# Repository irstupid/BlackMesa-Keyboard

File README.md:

# Keyboard Project

the first week of hack clubs half life thing.

i have a friend who asked me to make a keyboard for him and i was like "oh sure that sounds fun" and now i am finaly getting around to it

- it runs on a raspberry pi pico using QMK as its main firmware (more details in the firmware section once i do that)
- it is TKL
- it has 90 neopixle addressable LEDS
- it has a custom case (also unfinished, will update once done)

## THE PICO USB
after writing this section i realized i got maybe a little annoyed and crashed out a little, but im keeping it like this because i think its valid to get a little annoyed that my project has been rejected like four times for something i fixed three times ago, but dont take it personally, i completely understand you are probably trying to get through as many projects in as little time as possible and some things slip through the cracks

ok yall are really REALLY giving me hell about my pico usb placement and i have justified and explained how it will work like FOUR TIMES but im STILL REJECTED FOR IT so here we go again, if you reject me for this once again i swear to god i am going to just straight up leave this whole thing.

the board is suspended in the case:

the pico is attached to the bottom of the board. it is not colliding with the bottom of the case because the board is suspended. the usb can plug into the pico because the pico board has a thickness (1mm to be exact, specified by the datasheet here https://pip-assets.raspberrypi.com/categories/610-raspberry-pi-pico/documents/RP-008307-DS-3-pico-datasheet.pdf on page 7) and i have a usb plug that has a exterior thickness of less than 1mm, allowing it to fit between the pico and board:

the cable will exit the case through the back. this is a top view of the cable exiting the board. the cable runs bellow the PCB. I reiterate, THE PCB IS SUSPENDED. THERE IS SPACE BENEATH IT. THE CABLE GOES IN THAT SPACE:

this is a full side profile of the case. As you can see, the PCB is suspended by the key plate, the pico is soldered to the underside of the PCB, the cable plugs into the usb on the pcio, and the cable runs beneath the PCB and out of the case:

THIS. WILL. WORK. I am 100% sure this will work. i have sextuple checked all of my work. everything fits. IT. WILL. WORK. if you are incapable of understanding that i recommend going to the local kindergarten and retaking shapes and colors instead of failing me based on your incompetence. 

Also, you marked off my BOM for not including a SINGLE 6.3mm THT resisitor. You can find this resistor in literally any electronics kit ever. breadboards come with them, arduinos come with them, even fucking leds come with them. they are everywhere. my school has a literal cabinet full of them. i have a few thousand of them. i would be willing to bet that you have at least a few hundred of them to. you could probably find them laying on the street, i probably have 3 on my floor somewhere, i wouldn't be surprised if i have one inside of my body. you can find this SINGLE component basically anywhere. you can barely even buy them individually. they cost like literally less than a cent. here is a pack of 2600 of them for like $15 https://www.amazon.com/dp/B085NQZNTY?lv=shuf&channelId=500&plpRedirect=mhFallback. I am (obviously) supplying this myself. whats next? do i have to include the solder i intend to use for this project in my BOM? the electricity i use for the soldering iron? the wires i use to patch things together? the usb cable i use to program the pcio? because all of those things have a significantly bigger impact on the total cost of this project. it is a SINGLE FUCKING RESISTOR. ITS NOT EVEN A NECESSARY COMPONENT, it just helps debounce the address line (which is only like 30mm long so it barely matters). the resistance dosent mater. it could be anywhere between a 220 and a 10k resistor. i could probably construct this component myself with a paperclip. like im sorry for the crash out but seriously is this the hill you are going to kill me on? 

## Schematic

also here is the row/column layout if you were wondering

## PCB

i was initially going to add a silkscreen but ran out of inspiration and time. i might still do that it have have any ideas.
the BOM only has the board and none of the parts because i am sourcing those externally.
the usbc on the pico pointing inward is intentional, the cable will go along the bottom and through the back side of the case.

also sorry about not fixing the issues with the PCB i fixed them but then forgot to commit, everything should be updated now.

## Firmware
it will use QMK for the keyboard and some custom program for controlling the LEDS on a separate core.
i will work on the firmware once i have a pico and board to test on

## Case
the case will be made from a 3d printed part and a sanded acrylic key plate. here is a rough sketch

everything will be machined in house at my school. i will add more details once done

.

.

.

.

i was initially skeptical of markdowns but i actually really like how they handle formatting, i might start using them more. hopefully this readme is ok!

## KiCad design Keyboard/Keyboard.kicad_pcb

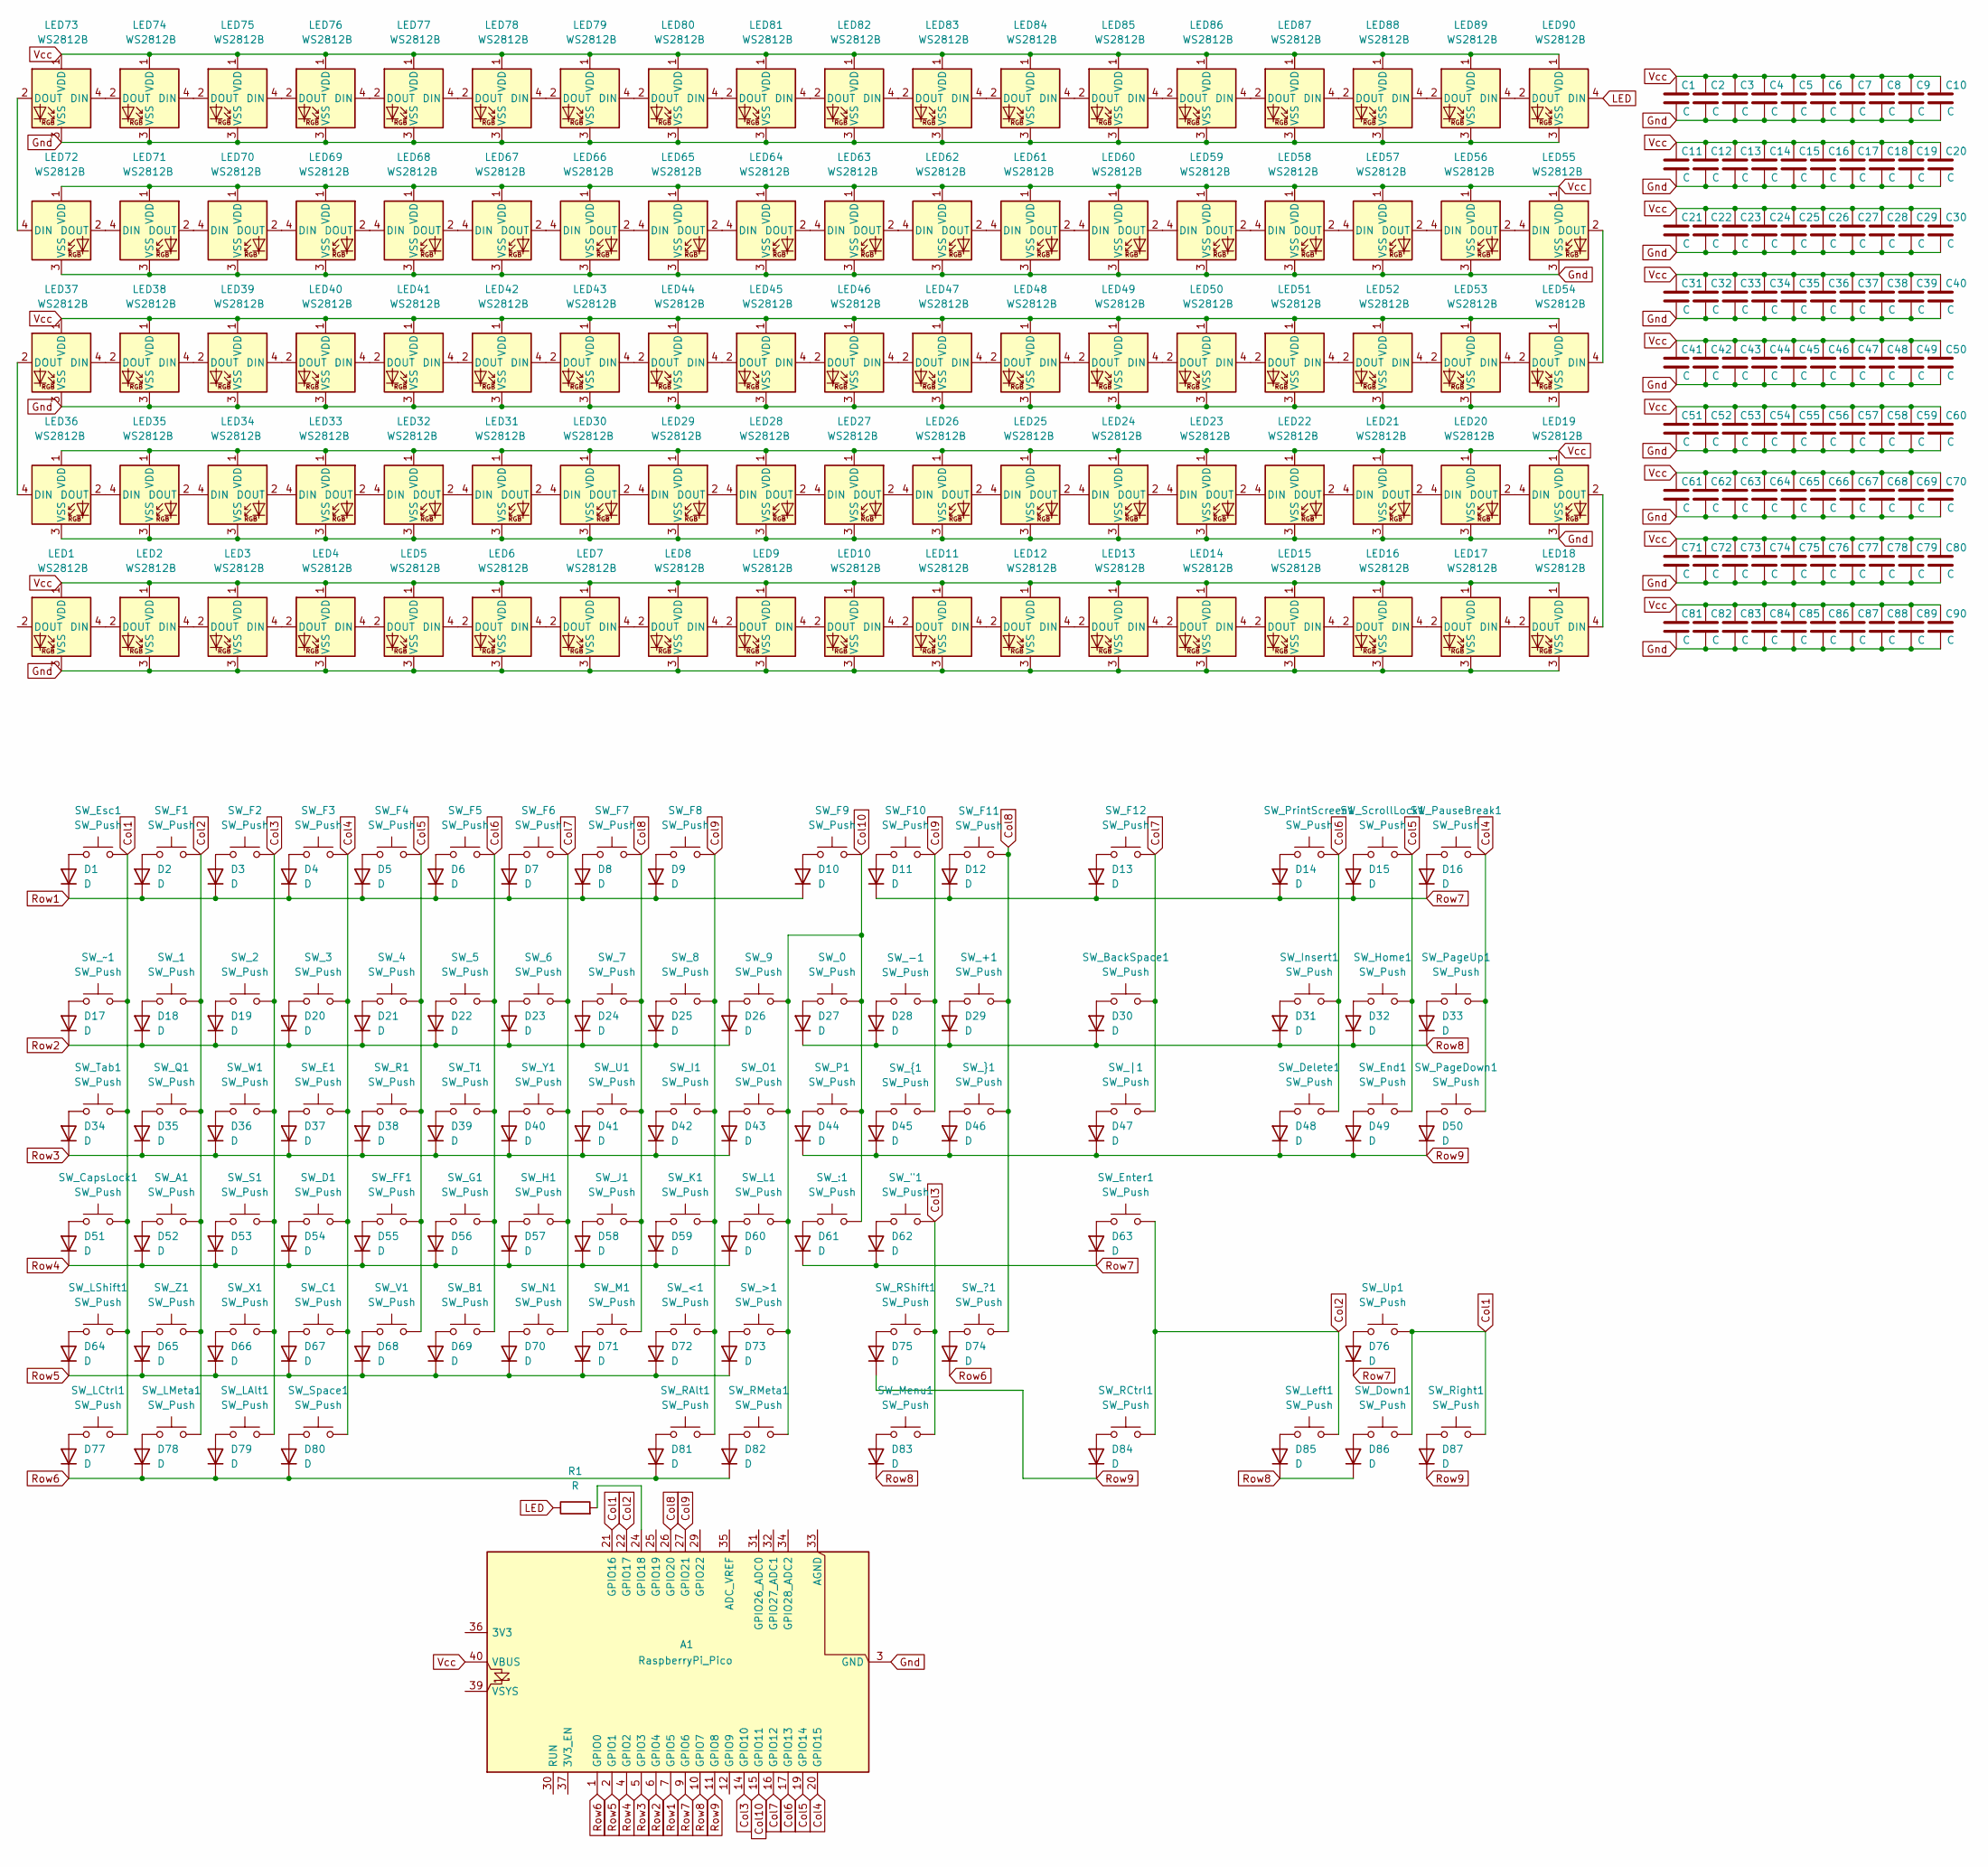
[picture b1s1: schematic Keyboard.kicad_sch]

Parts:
A1: RaspberryPi_Pico; RaspberryPi_Pico_Common_SMD
C1, C2, C3, C4, C5, C6, C7, C8, C9, C10, C11, C12, C13, C14, C15, C16, C17, C18, C19, C20, C21, C22, C23, C24, C25, C26, C27, C28, C29, C30, C31, C32, C33, C34, C35, C36, C37, C38, C39, C40, C41, C42, C43, C44, C45, C46, C47, C48, C49, C50, C51, C52, C53, C54, C55, C56, C57, C58, C59, C60, C61, C62, C63, C64, C65, C66, C67, C68, C69, C70, C71, C72, C73, C74, C75, C76, C77, C78, C79, C80, C81, C82, C83, C84, C85, C86, C87, C88, C89, C90: C; C_0201_0603Metric_Pad0.64x0.40mm_HandSolder
D1, D2, D3, D4, D5, D6, D7, D8, D9, D10, D11, D12, D13, D14, D15, D16, D17, D18, D19, D20, D21, D22, D23, D24, D25, D26, D27, D28, D29, D30, D31, D32, D33, D34, D35, D36, D37, D38, D39, D40, D41, D42, D43, D44, D45, D46, D47, D48, D49, D50, D51, D52, D53, D54, D55, D56, D57, D58, D59, D60, D61, D62, D63, D64, D65, D66, D67, D68, D69, D70, D71, D72, D73, D74, D75, D76, D77, D78, D79, D80, D81, D82, D83, D84, D85, D86, D87: D; D_SMA
LED1, LED2, LED3, LED4, LED5, LED6, LED7, LED8, LED9, LED10, LED11, LED12, LED13, LED14, LED15, LED16, LED17, LED18, LED19, LED20, LED21, LED22, LED23, LED24, LED25, LED26, LED27, LED28, LED29, LED30, LED31, LED32, LED33, LED34, LED35, LED36, LED37, LED38, LED39, LED40, LED41, LED42, LED43, LED44, LED45, LED46, LED47, LED48, LED49, LED50, LED51, LED52, LED53, LED54, LED55, LED56, LED57, LED58, LED59, LED60, LED61, LED62, LED63, LED64, LED65, LED66, LED67, LED68, LED69, LED70, LED71, LED72, LED73, LED74, LED75, LED76, LED77, LED78, LED79, LED80, LED81, LED82, LED83, LED84, LED85, LED86, LED87, LED88, LED89, LED90: WS2812B; LED_WS2812B_PLCC4_5.0x5.0mm_P3.2mm
R1: R; R_Axial_DIN0207_L6.3mm_D2.5mm_P7.62mm_Horizontal
SW_0, SW_1, SW_2, SW_3, SW_4, SW_5, SW_6, SW_7, SW_8, SW_9: SW_Push; SW_Cherry_MX_1.00u_PCB
SW_"1: SW_Push; SW_Cherry_MX_1.00u_PCB
SW_+1: SW_Push; SW_Cherry_MX_1.00u_PCB
SW_-1: SW_Push; SW_Cherry_MX_1.00u_PCB
SW_:1: SW_Push; SW_Cherry_MX_1.00u_PCB
SW_<1: SW_Push; SW_Cherry_MX_1.00u_PCB
SW_>1: SW_Push; SW_Cherry_MX_1.00u_PCB
SW_?1: SW_Push; SW_Cherry_MX_1.00u_PCB
SW_A1: SW_Push; SW_Cherry_MX_1.00u_PCB
SW_B1: SW_Push; SW_Cherry_MX_1.00u_PCB
SW_BackSpace1: SW_Push; SW_Cherry_MX_2.00u_PCB
SW_C1: SW_Push; SW_Cherry_MX_1.00u_PCB
SW_CapsLock1: SW_Push; SW_Cherry_MX_1.75u_PCB
SW_D1: SW_Push; SW_Cherry_MX_1.00u_PCB
SW_Delete1: SW_Push; SW_Cherry_MX_1.00u_PCB
SW_Down1: SW_Push; SW_Cherry_MX_1.00u_PCB
SW_E1: SW_Push; SW_Cherry_MX_1.00u_PCB
SW_End1: SW_Push; SW_Cherry_MX_1.00u_PCB
SW_Enter1: SW_Push; SW_Cherry_MX_2.25u_PCB
SW_Esc1: SW_Push; SW_Cherry_MX_1.00u_PCB
SW_F1, SW_F2, SW_F3, SW_F4, SW_F5, SW_F6, SW_F7, SW_F8, SW_F9, SW_F10, SW_F11, SW_F12: SW_Push; SW_Cherry_MX_1.00u_PCB
SW_FF1: SW_Push; SW_Cherry_MX_1.00u_PCB
SW_G1: SW_Push; SW_Cherry_MX_1.00u_PCB
SW_H1: SW_Push; SW_Cherry_MX_1.00u_PCB
SW_Home1: SW_Push; SW_Cherry_MX_1.00u_PCB
SW_I1: SW_Push; SW_Cherry_MX_1.00u_PCB
SW_Insert1: SW_Push; SW_Cherry_MX_1.00u_PCB
SW_J1: SW_Push; SW_Cherry_MX_1.00u_PCB
SW_K1: SW_Push; SW_Cherry_MX_1.00u_PCB
SW_L1: SW_Push; SW_Cherry_MX_1.00u_PCB
SW_LAlt1: SW_Push; SW_Cherry_MX_1.25u_PCB
SW_LCtrl1: SW_Push; SW_Cherry_MX_1.25u_PCB
SW_LMeta1: SW_Push; SW_Cherry_MX_1.25u_PCB
SW_LShift1: SW_Push; SW_Cherry_MX_2.25u_PCB
SW_Left1: SW_Push; SW_Cherry_MX_1.00u_PCB
SW_M1: SW_Push; SW_Cherry_MX_1.00u_PCB
SW_Menu1: SW_Push; SW_Cherry_MX_1.25u_Plate
SW_N1: SW_Push; SW_Cherry_MX_1.00u_PCB
SW_O1: SW_Push; SW_Cherry_MX_1.00u_PCB
SW_P1: SW_Push; SW_Cherry_MX_1.00u_PCB
SW_PageDown1: SW_Push; SW_Cherry_MX_1.00u_PCB
SW_PageUp1: SW_Push; SW_Cherry_MX_1.00u_PCB
SW_PauseBreak1: SW_Push; SW_Cherry_MX_1.00u_PCB
SW_PrintScreen1: SW_Push; SW_Cherry_MX_1.00u_PCB
SW_Q1: SW_Push; SW_Cherry_MX_1.00u_PCB
SW_R1: SW_Push; SW_Cherry_MX_1.00u_PCB
SW_RAlt1: SW_Push; SW_Cherry_MX_1.25u_PCB
SW_RCtrl1: SW_Push; SW_Cherry_MX_1.25u_PCB
SW_RMeta1: SW_Push; SW_Cherry_MX_1.25u_PCB
SW_RShift1: SW_Push; SW_Cherry_MX_2.75u_PCB
SW_Right1: SW_Push; SW_Cherry_MX_1.00u_PCB
SW_S1: SW_Push; SW_Cherry_MX_1.00u_PCB
SW_ScrollLock1: SW_Push; SW_Cherry_MX_1.00u_PCB
SW_Space1: SW_Push; SW_Cherry_MX_6.25u_PCB
SW_T1: SW_Push; SW_Cherry_MX_1.00u_PCB
SW_Tab1: SW_Push; SW_Cherry_MX_1.50u_PCB
SW_U1: SW_Push; SW_Cherry_MX_1.00u_PCB
SW_Up1: SW_Push; SW_Cherry_MX_1.00u_PCB
SW_V1: SW_Push; SW_Cherry_MX_1.00u_PCB
SW_W1: SW_Push; SW_Cherry_MX_1.00u_PCB
SW_X1: SW_Push; SW_Cherry_MX_1.00u_PCB
SW_Y1: SW_Push; SW_Cherry_MX_1.00u_PCB
SW_Z1: SW_Push; SW_Cherry_MX_1.00u_PCB
SW_{1: SW_Push; SW_Cherry_MX_1.00u_PCB
SW_|1: SW_Push; SW_Cherry_MX_1.50u_PCB
SW_}1: SW_Push; SW_Cherry_MX_1.00u_PCB
SW_~1: SW_Push; SW_Cherry_MX_1.00u_PCB

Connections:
Col1: A1.21 (GPIO16), SW_CapsLock1.1, SW_Down1.1, SW_Esc1.1, SW_LCtrl1.1, SW_LShift1.1, SW_Right1.1, SW_Tab1.1, SW_Up1.1, SW_~1.1
Col2: A1.22 (GPIO17), SW_1.1, SW_A1.1, SW_Enter1.1, SW_F1.1, SW_LMeta1.1, SW_Left1.1, SW_Q1.1, SW_RCtrl1.1, SW_Z1.1
Col3: A1.14 (GPIO10), SW_2.1, SW_"1.1, SW_F2.1, SW_LAlt1.1, SW_Menu1.1, SW_RShift1.1, SW_S1.1, SW_W1.1, SW_X1.1
Col4: A1.20 (GPIO15), SW_3.1, SW_C1.1, SW_D1.1, SW_E1.1, SW_F3.1, SW_PageDown1.1, SW_PageUp1.1, SW_PauseBreak1.1, SW_Space1.1
Col5: A1.19 (GPIO14), SW_4.1, SW_End1.1, SW_F4.1, SW_FF1.1, SW_Home1.1, SW_R1.1, SW_ScrollLock1.1, SW_V1.1
Col6: A1.17 (GPIO13), SW_5.1, SW_B1.1, SW_Delete1.1, SW_F5.1, SW_G1.1, SW_Insert1.1, SW_PrintScreen1.1, SW_T1.1
Col7: A1.16 (GPIO12), SW_6.1, SW_BackSpace1.1, SW_F6.1, SW_F12.1, SW_H1.1, SW_N1.1, SW_Y1.1, SW_|1.1
Col8: A1.26 (GPIO20), SW_7.1, SW_+1.1, SW_?1.1, SW_F7.1, SW_F11.1, SW_J1.1, SW_M1.1, SW_U1.1, SW_}1.1
Col9: A1.27 (GPIO21), SW_8.1, SW_-1.1, SW_<1.1, SW_F8.1, SW_F10.1, SW_I1.1, SW_K1.1, SW_RAlt1.1, SW_{1.1
Col10: A1.15 (GPIO11), SW_0.1, SW_9.1, SW_:1.1, SW_>1.1, SW_F9.1, SW_L1.1, SW_O1.1, SW_P1.1, SW_RMeta1.1
Gnd: A1.3 (GND), A1.8 (GND), A1.13 (GND), A1.18 (GND), A1.23 (GND), A1.28 (GND), A1.38 (GND), C1.2, C2.2, C3.2, C4.2, C5.2, C6.2, C7.2, C8.2, C9.2, C10.2, C11.2, C12.2, C13.2, C14.2, C15.2, C16.2, C17.2, C18.2, C19.2, C20.2, C21.2, C22.2, C23.2, C24.2, C25.2, C26.2, C27.2, C28.2, C29.2, C30.2, C31.2, C32.2, C33.2, C34.2, C35.2, C36.2, C37.2, C38.2, C39.2, C40.2, C41.2, C42.2, C43.2, C44.2, C45.2, C46.2, C47.2, C48.2, C49.2, C50.2, C51.2, C52.2, C53.2, C54.2, C55.2, C56.2, C57.2, C58.2, C59.2, C60.2, C61.2, C62.2, C63.2, C64.2, C65.2, C66.2, C67.2, C68.2, C69.2, C70.2, C71.2, C72.2, C73.2, C74.2, C75.2, C76.2, C77.2, C78.2, C79.2, C80.2, C81.2, C82.2, C83.2, C84.2, C85.2, C86.2, C87.2, C88.2, C89.2, C90.2, LED1.3 (VSS), LED2.3 (VSS), LED3.3 (VSS), LED4.3 (VSS), LED5.3 (VSS), LED6.3 (VSS), LED7.3 (VSS), LED8.3 (VSS), LED9.3 (VSS), LED10.3 (VSS), LED11.3 (VSS), LED12.3 (VSS), LED13.3 (VSS), LED14.3 (VSS), LED15.3 (VSS), LED16.3 (VSS), LED17.3 (VSS), LED18.3 (VSS), LED19.3 (VSS), LED20.3 (VSS), LED21.3 (VSS), LED22.3 (VSS), LED23.3 (VSS), LED24.3 (VSS), LED25.3 (VSS), LED26.3 (VSS), LED27.3 (VSS), LED28.3 (VSS), LED29.3 (VSS), LED30.3 (VSS), LED31.3 (VSS), LED32.3 (VSS), LED33.3 (VSS), LED34.3 (VSS), LED35.3 (VSS), LED36.3 (VSS), LED37.3 (VSS), LED38.3 (VSS), LED39.3 (VSS), LED40.3 (VSS), LED41.3 (VSS), LED42.3 (VSS), LED43.3 (VSS), LED44.3 (VSS), LED45.3 (VSS), LED46.3 (VSS), LED47.3 (VSS), LED48.3 (VSS), LED49.3 (VSS), LED50.3 (VSS), LED51.3 (VSS), LED52.3 (VSS), LED53.3 (VSS), LED54.3 (VSS), LED55.3 (VSS), LED56.3 (VSS), LED57.3 (VSS), LED58.3 (VSS), LED59.3 (VSS), LED60.3 (VSS), LED61.3 (VSS), LED62.3 (VSS), LED63.3 (VSS), LED64.3 (VSS), LED65.3 (VSS), LED66.3 (VSS), LED67.3 (VSS), LED68.3 (VSS), LED69.3 (VSS), LED70.3 (VSS), LED71.3 (VSS), LED72.3 (VSS), LED73.3 (VSS), LED74.3 (VSS), LED75.3 (VSS), LED76.3 (VSS), LED77.3 (VSS), LED78.3 (VSS), LED79.3 (VSS), LED80.3 (VSS), LED81.3 (VSS), LED82.3 (VSS), LED83.3 (VSS), LED84.3 (VSS), LED85.3 (VSS), LED86.3 (VSS), LED87.3 (VSS), LED88.3 (VSS), LED89.3 (VSS), LED90.3 (VSS)
LED: LED90.4 (DIN), R1.1
unnamed: A1.24 (GPIO18), R1.2
unnamed: D1.2 (A), SW_Esc1.2
unnamed: D2.2 (A), SW_F1.2
unnamed: D3.2 (A), SW_F2.2
unnamed: D4.2 (A), SW_F3.2
unnamed: D5.2 (A), SW_F4.2
unnamed: D6.2 (A), SW_F5.2
unnamed: D7.2 (A), SW_F6.2
unnamed: D8.2 (A), SW_F7.2
unnamed: D9.2 (A), SW_F8.2
unnamed: D10.2 (A), SW_F9.2
unnamed: D11.2 (A), SW_F10.2
unnamed: D12.2 (A), SW_F11.2
unnamed: D13.2 (A), SW_F12.2
unnamed: D14.2 (A), SW_PrintScreen1.2
unnamed: D15.2 (A), SW_ScrollLock1.2
unnamed: D16.2 (A), SW_PauseBreak1.2
unnamed: D17.2 (A), SW_~1.2
unnamed: D18.2 (A), SW_1.2
unnamed: D19.2 (A), SW_2.2
unnamed: D20.2 (A), SW_3.2
unnamed: D21.2 (A), SW_4.2
unnamed: D22.2 (A), SW_5.2
unnamed: D23.2 (A), SW_6.2
unnamed: D24.2 (A), SW_7.2
unnamed: D25.2 (A), SW_8.2
unnamed: D26.2 (A), SW_9.2
unnamed: D27.2 (A), SW_0.2
unnamed: D28.2 (A), SW_-1.2
unnamed: D29.2 (A), SW_+1.2
unnamed: D30.2 (A), SW_BackSpace1.2
unnamed: D31.2 (A), SW_Insert1.2
unnamed: D32.2 (A), SW_Home1.2
unnamed: D33.2 (A), SW_PageUp1.2
unnamed: D34.2 (A), SW_Tab1.2
unnamed: D35.2 (A), SW_Q1.2
unnamed: D36.2 (A), SW_W1.2
unnamed: D37.2 (A), SW_E1.2
unnamed: D38.2 (A), SW_R1.2
unnamed: D39.2 (A), SW_T1.2
unnamed: D40.2 (A), SW_Y1.2
unnamed: D41.2 (A), SW_U1.2
unnamed: D42.2 (A), SW_I1.2
unnamed: D43.2 (A), SW_O1.2
unnamed: D44.2 (A), SW_P1.2
unnamed: D45.2 (A), SW_{1.2
unnamed: D46.2 (A), SW_}1.2
unnamed: D47.2 (A), SW_|1.2
unnamed: D48.2 (A), SW_Delete1.2
unnamed: D49.2 (A), SW_End1.2
unnamed: D50.2 (A), SW_PageDown1.2
unnamed: D51.2 (A), SW_CapsLock1.2
unnamed: D52.2 (A), SW_A1.2
unnamed: D53.2 (A), SW_S1.2
unnamed: D54.2 (A), SW_D1.2
unnamed: D55.2 (A), SW_FF1.2
unnamed: D56.2 (A), SW_G1.2
unnamed: D57.2 (A), SW_H1.2
unnamed: D58.2 (A), SW_J1.2
unnamed: D59.2 (A), SW_K1.2
unnamed: D60.2 (A), SW_L1.2
unnamed: D61.2 (A), SW_:1.2
unnamed: D62.2 (A), SW_"1.2
unnamed: D63.2 (A), SW_Enter1.2
unnamed: D64.2 (A), SW_LShift1.2
unnamed: D65.2 (A), SW_Z1.2
unnamed: D66.2 (A), SW_X1.2
unnamed: D67.2 (A), SW_C1.2
unnamed: D68.2 (A), SW_V1.2
unnamed: D69.2 (A), SW_B1.2
unnamed: D70.2 (A), SW_N1.2
unnamed: D71.2 (A), SW_M1.2
unnamed: D72.2 (A), SW_<1.2
unnamed: D73.2 (A), SW_>1.2
unnamed: D74.2 (A), SW_?1.2
unnamed: D75.2 (A), SW_RShift1.2
unnamed: D76.2 (A), SW_Up1.2
unnamed: D77.2 (A), SW_LCtrl1.2
unnamed: D78.2 (A), SW_LMeta1.2
unnamed: D79.2 (A), SW_LAlt1.2
unnamed: D80.2 (A), SW_Space1.2
unnamed: D81.2 (A), SW_RAlt1.2
unnamed: D82.2 (A), SW_RMeta1.2
unnamed: D83.2 (A), SW_Menu1.2
unnamed: D84.2 (A), SW_RCtrl1.2
unnamed: D85.2 (A), SW_Left1.2
unnamed: D86.2 (A), SW_Down1.2
unnamed: D87.2 (A), SW_Right1.2
unnamed: LED1.4 (DIN), LED2.2 (DOUT)
unnamed: LED2.4 (DIN), LED3.2 (DOUT)
unnamed: LED3.4 (DIN), LED4.2 (DOUT)
unnamed: LED4.4 (DIN), LED5.2 (DOUT)
unnamed: LED5.4 (DIN), LED6.2 (DOUT)
unnamed: LED6.4 (DIN), LED7.2 (DOUT)
unnamed: LED7.4 (DIN), LED8.2 (DOUT)
unnamed: LED8.4 (DIN), LED9.2 (DOUT)
unnamed: LED10.4 (DIN), LED11.2 (DOUT)
unnamed: LED9.4 (DIN), LED10.2 (DOUT)
unnamed: LED11.4 (DIN), LED12.2 (DOUT)
unnamed: LED12.4 (DIN), LED13.2 (DOUT)
unnamed: LED13.4 (DIN), LED14.2 (DOUT)
unnamed: LED14.4 (DIN), LED15.2 (DOUT)
unnamed: LED15.4 (DIN), LED16.2 (DOUT)
unnamed: LED16.4 (DIN), LED17.2 (DOUT)
unnamed: LED17.4 (DIN), LED18.2 (DOUT)
unnamed: LED18.4 (DIN), LED19.2 (DOUT)
unnamed: LED19.4 (DIN), LED20.2 (DOUT)
unnamed: LED20.4 (DIN), LED21.2 (DOUT)
unnamed: LED21.4 (DIN), LED22.2 (DOUT)
unnamed: LED22.4 (DIN), LED23.2 (DOUT)
unnamed: LED23.4 (DIN), LED24.2 (DOUT)
unnamed: LED24.4 (DIN), LED25.2 (DOUT)
unnamed: LED25.4 (DIN), LED26.2 (DOUT)
unnamed: LED26.4 (DIN), LED27.2 (DOUT)
unnamed: LED27.4 (DIN), LED28.2 (DOUT)
unnamed: LED28.4 (DIN), LED29.2 (DOUT)
unnamed: LED29.4 (DIN), LED30.2 (DOUT)
unnamed: LED30.4 (DIN), LED31.2 (DOUT)
unnamed: LED31.4 (DIN), LED32.2 (DOUT)
unnamed: LED32.4 (DIN), LED33.2 (DOUT)
unnamed: LED33.4 (DIN), LED34.2 (DOUT)
unnamed: LED34.4 (DIN), LED35.2 (DOUT)
unnamed: LED35.4 (DIN), LED36.2 (DOUT)
unnamed: LED36.4 (DIN), LED37.2 (DOUT)
unnamed: LED37.4 (DIN), LED38.2 (DOUT)
unnamed: LED38.4 (DIN), LED39.2 (DOUT)
unnamed: LED39.4 (DIN), LED40.2 (DOUT)
unnamed: LED40.4 (DIN), LED41.2 (DOUT)
unnamed: LED41.4 (DIN), LED42.2 (DOUT)
unnamed: LED42.4 (DIN), LED43.2 (DOUT)
unnamed: LED43.4 (DIN), LED44.2 (DOUT)
unnamed: LED44.4 (DIN), LED45.2 (DOUT)
unnamed: LED45.4 (DIN), LED46.2 (DOUT)
unnamed: LED46.4 (DIN), LED47.2 (DOUT)
unnamed: LED47.4 (DIN), LED48.2 (DOUT)
unnamed: LED48.4 (DIN), LED49.2 (DOUT)
unnamed: LED49.4 (DIN), LED50.2 (DOUT)
unnamed: LED50.4 (DIN), LED51.2 (DOUT)
unnamed: LED51.4 (DIN), LED52.2 (DOUT)
unnamed: LED52.4 (DIN), LED53.2 (DOUT)
unnamed: LED53.4 (DIN), LED54.2 (DOUT)
unnamed: LED54.4 (DIN), LED55.2 (DOUT)
unnamed: LED55.4 (DIN), LED56.2 (DOUT)
unnamed: LED56.4 (DIN), LED57.2 (DOUT)
unnamed: LED57.4 (DIN), LED58.2 (DOUT)
unnamed: LED58.4 (DIN), LED59.2 (DOUT)
unnamed: LED59.4 (DIN), LED60.2 (DOUT)
unnamed: LED60.4 (DIN), LED61.2 (DOUT)
unnamed: LED61.4 (DIN), LED62.2 (DOUT)
unnamed: LED62.4 (DIN), LED63.2 (DOUT)
unnamed: LED63.4 (DIN), LED64.2 (DOUT)
unnamed: LED64.4 (DIN), LED65.2 (DOUT)
unnamed: LED65.4 (DIN), LED66.2 (DOUT)
unnamed: LED66.4 (DIN), LED67.2 (DOUT)
unnamed: LED67.4 (DIN), LED68.2 (DOUT)
unnamed: LED68.4 (DIN), LED69.2 (DOUT)
unnamed: LED69.4 (DIN), LED70.2 (DOUT)
unnamed: LED70.4 (DIN), LED71.2 (DOUT)
unnamed: LED71.4 (DIN), LED72.2 (DOUT)
unnamed: LED72.4 (DIN), LED73.2 (DOUT)
unnamed: LED73.4 (DIN), LED74.2 (DOUT)
unnamed: LED74.4 (DIN), LED75.2 (DOUT)
unnamed: LED75.4 (DIN), LED76.2 (DOUT)
unnamed: LED76.4 (DIN), LED77.2 (DOUT)
unnamed: LED77.4 (DIN), LED78.2 (DOUT)
unnamed: LED78.4 (DIN), LED79.2 (DOUT)
unnamed: LED79.4 (DIN), LED80.2 (DOUT)
unnamed: LED80.4 (DIN), LED81.2 (DOUT)
unnamed: LED81.4 (DIN), LED82.2 (DOUT)
unnamed: LED82.4 (DIN), LED83.2 (DOUT)
unnamed: LED83.4 (DIN), LED84.2 (DOUT)
unnamed: LED84.4 (DIN), LED85.2 (DOUT)
unnamed: LED85.4 (DIN), LED86.2 (DOUT)
unnamed: LED86.4 (DIN), LED87.2 (DOUT)
unnamed: LED87.4 (DIN), LED88.2 (DOUT)
unnamed: LED88.4 (DIN), LED89.2 (DOUT)
unnamed: LED89.4 (DIN), LED90.2 (DOUT)
Row1: A1.7 (GPIO5), D1.1 (K), D2.1 (K), D3.1 (K), D4.1 (K), D5.1 (K), D6.1 (K), D7.1 (K), D8.1 (K), D9.1 (K), D10.1 (K)
Row2: A1.6 (GPIO4), D17.1 (K), D18.1 (K), D19.1 (K), D20.1 (K), D21.1 (K), D22.1 (K), D23.1 (K), D24.1 (K), D25.1 (K), D26.1 (K)
Row3: A1.5 (GPIO3), D34.1 (K), D35.1 (K), D36.1 (K), D37.1 (K), D38.1 (K), D39.1 (K), D40.1 (K), D41.1 (K), D42.1 (K), D43.1 (K)
Row4: A1.4 (GPIO2), D51.1 (K), D52.1 (K), D53.1 (K), D54.1 (K), D55.1 (K), D56.1 (K), D57.1 (K), D58.1 (K), D59.1 (K), D60.1 (K)
Row5: A1.2 (GPIO1), D64.1 (K), D65.1 (K), D66.1 (K), D67.1 (K), D68.1 (K), D69.1 (K), D70.1 (K), D71.1 (K), D72.1 (K), D73.1 (K)
Row6: A1.1 (GPIO0), D74.1 (K), D77.1 (K), D78.1 (K), D79.1 (K), D80.1 (K), D81.1 (K), D82.1 (K)
Row7: A1.9 (GPIO6), D11.1 (K), D12.1 (K), D13.1 (K), D14.1 (K), D15.1 (K), D16.1 (K), D61.1 (K), D62.1 (K), D63.1 (K), D76.1 (K)
Row8: A1.10 (GPIO7), D27.1 (K), D28.1 (K), D29.1 (K), D30.1 (K), D31.1 (K), D32.1 (K), D33.1 (K), D83.1 (K), D85.1 (K), D86.1 (K)
Row9: A1.11 (GPIO8), D44.1 (K), D45.1 (K), D46.1 (K), D47.1 (K), D48.1 (K), D49.1 (K), D50.1 (K), D75.1 (K), D84.1 (K), D87.1 (K)
Vcc: A1.40 (VBUS), C1.1, C2.1, C3.1, C4.1, C5.1, C6.1, C7.1, C8.1, C9.1, C10.1, C11.1, C12.1, C13.1, C14.1, C15.1, C16.1, C17.1, C18.1, C19.1, C20.1, C21.1, C22.1, C23.1, C24.1, C25.1, C26.1, C27.1, C28.1, C29.1, C30.1, C31.1, C32.1, C33.1, C34.1, C35.1, C36.1, C37.1, C38.1, C39.1, C40.1, C41.1, C42.1, C43.1, C44.1, C45.1, C46.1, C47.1, C48.1, C49.1, C50.1, C51.1, C52.1, C53.1, C54.1, C55.1, C56.1, C57.1, C58.1, C59.1, C60.1, C61.1, C62.1, C63.1, C64.1, C65.1, C66.1, C67.1, C68.1, C69.1, C70.1, C71.1, C72.1, C73.1, C74.1, C75.1, C76.1, C77.1, C78.1, C79.1, C80.1, C81.1, C82.1, C83.1, C84.1, C85.1, C86.1, C87.1, C88.1, C89.1, C90.1, LED1.1 (VDD), LED2.1 (VDD), LED3.1 (VDD), LED4.1 (VDD), LED5.1 (VDD), LED6.1 (VDD), LED7.1 (VDD), LED8.1 (VDD), LED9.1 (VDD), LED10.1 (VDD), LED11.1 (VDD), LED12.1 (VDD), LED13.1 (VDD), LED14.1 (VDD), LED15.1 (VDD), LED16.1 (VDD), LED17.1 (VDD), LED18.1 (VDD), LED19.1 (VDD), LED20.1 (VDD), LED21.1 (VDD), LED22.1 (VDD), LED23.1 (VDD), LED24.1 (VDD), LED25.1 (VDD), LED26.1 (VDD), LED27.1 (VDD), LED28.1 (VDD), LED29.1 (VDD), LED30.1 (VDD), LED31.1 (VDD), LED32.1 (VDD), LED33.1 (VDD), LED34.1 (VDD), LED35.1 (VDD), LED36.1 (VDD), LED37.1 (VDD), LED38.1 (VDD), LED39.1 (VDD), LED40.1 (VDD), LED41.1 (VDD), LED42.1 (VDD), LED43.1 (VDD), LED44.1 (VDD), LED45.1 (VDD), LED46.1 (VDD), LED47.1 (VDD), LED48.1 (VDD), LED49.1 (VDD), LED50.1 (VDD), LED51.1 (VDD), LED52.1 (VDD), LED53.1 (VDD), LED54.1 (VDD), LED55.1 (VDD), LED56.1 (VDD), LED57.1 (VDD), LED58.1 (VDD), LED59.1 (VDD), LED60.1 (VDD), LED61.1 (VDD), LED62.1 (VDD), LED63.1 (VDD), LED64.1 (VDD), LED65.1 (VDD), LED66.1 (VDD), LED67.1 (VDD), LED68.1 (VDD), LED69.1 (VDD), LED70.1 (VDD), LED71.1 (VDD), LED72.1 (VDD), LED73.1 (VDD), LED74.1 (VDD), LED75.1 (VDD), LED76.1 (VDD), LED77.1 (VDD), LED78.1 (VDD), LED79.1 (VDD), LED80.1 (VDD), LED81.1 (VDD), LED82.1 (VDD), LED83.1 (VDD), LED84.1 (VDD), LED85.1 (VDD), LED86.1 (VDD), LED87.1 (VDD), LED88.1 (VDD), LED89.1 (VDD), LED90.1 (VDD)

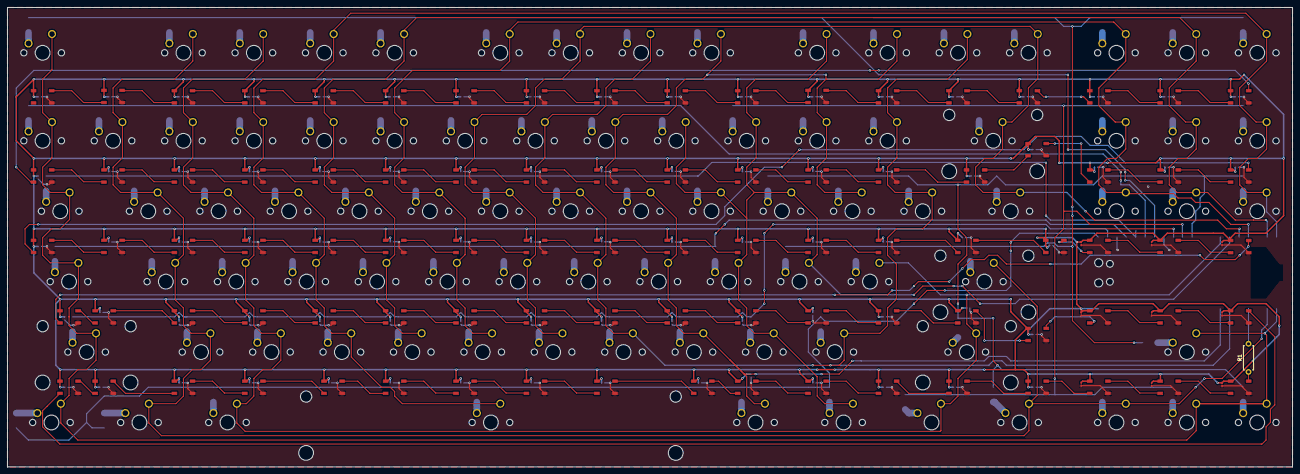
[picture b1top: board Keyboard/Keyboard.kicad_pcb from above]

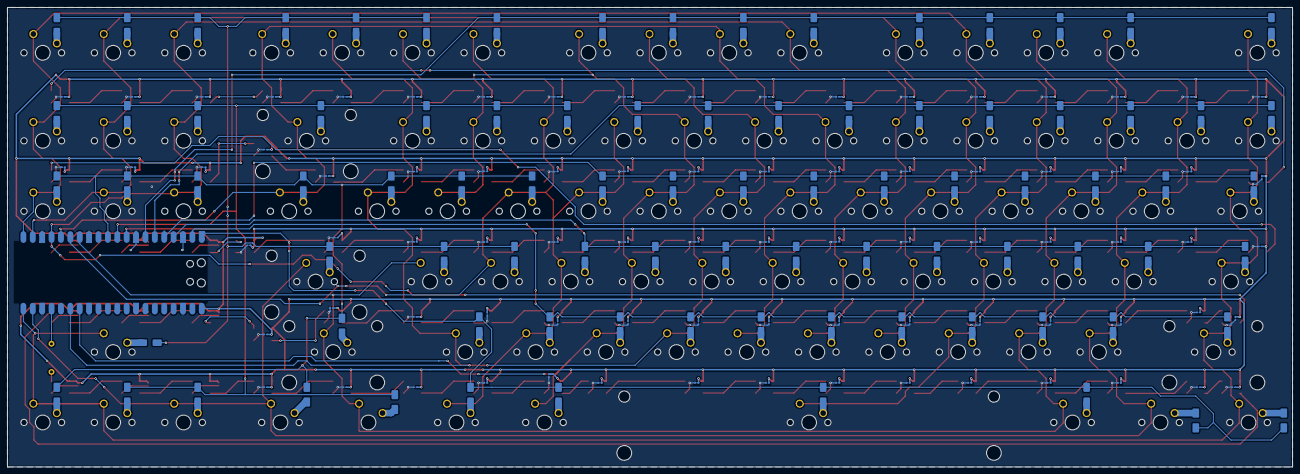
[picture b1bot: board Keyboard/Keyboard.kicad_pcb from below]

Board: 2 copper layers, 347.7 x 124.3 mm, 356 parts (169 on the bottom side), 199 nets.

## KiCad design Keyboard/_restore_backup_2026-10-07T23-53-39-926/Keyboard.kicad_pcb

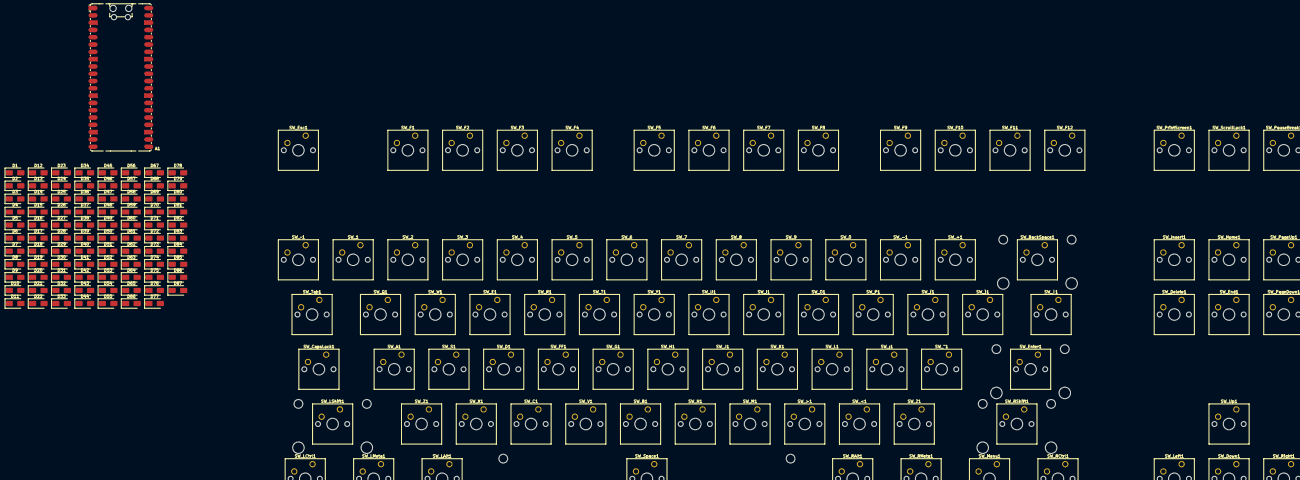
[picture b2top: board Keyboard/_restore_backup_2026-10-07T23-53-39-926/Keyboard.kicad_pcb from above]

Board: 2 copper layers, 175 parts (0 on the bottom side), 108 nets, no tracks yet.

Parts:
A1: RaspberryPi_Pico; RaspberryPi_Pico_Common_SMD
D1, D2, D3, D4, D5, D6, D7, D8, D9, D10, D11, D12, D13, D14, D15, D16, D17, D18, D19, D20, D21, D22, D23, D24, D25, D26, D27, D28, D29, D30, D31, D32, D33, D34, D35, D36, D37, D38, D39, D40, D41, D42, D43, D44, D45, D46, D47, D48, D49, D50, D51, D52, D53, D54, D55, D56, D57, D58, D59, D60, D61, D62, D63, D64, D65, D66, D67, D68, D69, D70, D71, D72, D73, D74, D75, D76, D77, D78, D79, D80, D81, D82, D83, D84, D85, D86, D87: D; D_SMA
SW_0, SW_1, SW_2, SW_3, SW_4, SW_5, SW_6, SW_7, SW_8, SW_9: SW_Push; SW_Cherry_MX_1.00u_PCB
SW_"1: SW_Push; SW_Cherry_MX_1.00u_PCB
SW_+1: SW_Push; SW_Cherry_MX_1.00u_PCB
SW_-1: SW_Push; SW_Cherry_MX_1.00u_PCB
SW_:1: SW_Push; SW_Cherry_MX_1.00u_PCB
SW_<1: SW_Push; SW_Cherry_MX_1.00u_PCB
SW_>1: SW_Push; SW_Cherry_MX_1.00u_PCB
SW_?1: SW_Push; SW_Cherry_MX_1.00u_PCB
SW_A1: SW_Push; SW_Cherry_MX_1.00u_PCB
SW_B1: SW_Push; SW_Cherry_MX_1.00u_PCB
SW_BackSpace1: SW_Push; SW_Cherry_MX_2.00u_PCB
SW_C1: SW_Push; SW_Cherry_MX_1.00u_PCB
SW_CapsLock1: SW_Push; SW_Cherry_MX_1.75u_PCB
SW_D1: SW_Push; SW_Cherry_MX_1.00u_PCB
SW_Delete1: SW_Push; SW_Cherry_MX_1.00u_PCB
SW_Down1: SW_Push; SW_Cherry_MX_1.00u_PCB
SW_E1: SW_Push; SW_Cherry_MX_1.00u_PCB
SW_End1: SW_Push; SW_Cherry_MX_1.00u_PCB
SW_Enter1: SW_Push; SW_Cherry_MX_2.25u_PCB
SW_Esc1: SW_Push; SW_Cherry_MX_1.00u_PCB
SW_F1, SW_F2, SW_F3, SW_F4, SW_F5, SW_F6, SW_F7, SW_F8, SW_F9, SW_F10, SW_F11, SW_F12: SW_Push; SW_Cherry_MX_1.00u_PCB
SW_FF1: SW_Push; SW_Cherry_MX_1.00u_PCB
SW_G1: SW_Push; SW_Cherry_MX_1.00u_PCB
SW_H1: SW_Push; SW_Cherry_MX_1.00u_PCB
SW_Home1: SW_Push; SW_Cherry_MX_1.00u_PCB
SW_I1: SW_Push; SW_Cherry_MX_1.00u_PCB
SW_Insert1: SW_Push; SW_Cherry_MX_1.00u_PCB
SW_J1: SW_Push; SW_Cherry_MX_1.00u_PCB
SW_K1: SW_Push; SW_Cherry_MX_1.00u_PCB
SW_L1: SW_Push; SW_Cherry_MX_1.00u_PCB
SW_LAlt1: SW_Push; SW_Cherry_MX_1.25u_PCB
SW_LCtrl1: SW_Push; SW_Cherry_MX_1.25u_PCB
SW_LMeta1: SW_Push; SW_Cherry_MX_1.25u_PCB
SW_LShift1: SW_Push; SW_Cherry_MX_2.25u_PCB
SW_Left1: SW_Push; SW_Cherry_MX_1.00u_PCB
SW_M1: SW_Push; SW_Cherry_MX_1.00u_PCB
SW_Menu1: SW_Push; SW_Cherry_MX_1.25u_Plate
SW_N1: SW_Push; SW_Cherry_MX_1.00u_PCB
SW_O1: SW_Push; SW_Cherry_MX_1.00u_PCB
SW_P1: SW_Push; SW_Cherry_MX_1.00u_PCB
SW_PageDown1: SW_Push; SW_Cherry_MX_1.00u_PCB
SW_PageUp1: SW_Push; SW_Cherry_MX_1.00u_PCB
SW_PauseBreak1: SW_Push; SW_Cherry_MX_1.00u_PCB
SW_PrintScreen1: SW_Push; SW_Cherry_MX_1.00u_PCB
SW_Q1: SW_Push; SW_Cherry_MX_1.00u_PCB
SW_R1: SW_Push; SW_Cherry_MX_1.00u_PCB
SW_RAlt1: SW_Push; SW_Cherry_MX_1.25u_PCB
SW_RCtrl1: SW_Push; SW_Cherry_MX_1.25u_PCB
SW_RMeta1: SW_Push; SW_Cherry_MX_1.25u_PCB
SW_RShift1: SW_Push; SW_Cherry_MX_2.75u_PCB
SW_Right1: SW_Push; SW_Cherry_MX_1.00u_PCB
SW_S1: SW_Push; SW_Cherry_MX_1.00u_PCB
SW_ScrollLock1: SW_Push; SW_Cherry_MX_1.00u_PCB
SW_Space1: SW_Push; SW_Cherry_MX_6.25u_PCB
SW_T1: SW_Push; SW_Cherry_MX_1.00u_PCB
SW_Tab1: SW_Push; SW_Cherry_MX_1.50u_PCB
SW_U1: SW_Push; SW_Cherry_MX_1.00u_PCB
SW_Up1: SW_Push; SW_Cherry_MX_1.00u_PCB
SW_V1: SW_Push; SW_Cherry_MX_1.00u_PCB
SW_W1: SW_Push; SW_Cherry_MX_1.00u_PCB
SW_X1: SW_Push; SW_Cherry_MX_1.00u_PCB
SW_Y1: SW_Push; SW_Cherry_MX_1.00u_PCB
SW_Z1: SW_Push; SW_Cherry_MX_1.00u_PCB
SW_{1: SW_Push; SW_Cherry_MX_1.00u_PCB
SW_|1: SW_Push; SW_Cherry_MX_1.50u_PCB
SW_}1: SW_Push; SW_Cherry_MX_1.00u_PCB
SW_~1: SW_Push; SW_Cherry_MX_1.00u_PCB

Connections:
Col1: SW_CapsLock1.2, SW_Down1.2, SW_Esc1.2, SW_LCtrl1.2, SW_LShift1.2, SW_Right1.2, SW_Tab1.2, SW_Up1.2, SW_~1.2
Col2: SW_1.2, SW_A1.2, SW_Enter1.2, SW_F1.2, SW_LMeta1.2, SW_Left1.2, SW_Q1.2, SW_RCtrl1.2, SW_Z1.2
Col3: SW_2.2, SW_"1.2, SW_F2.2, SW_LAlt1.2, SW_Menu1.2, SW_RShift1.2, SW_S1.2, SW_W1.2, SW_X1.2
Col4: SW_3.2, SW_C1.2, SW_D1.2, SW_E1.2, SW_F3.2, SW_PageDown1.2, SW_PageUp1.2, SW_PauseBreak1.2, SW_Space1.2
Col5: SW_4.2, SW_End1.2, SW_F4.2, SW_FF1.2, SW_Home1.2, SW_R1.2, SW_ScrollLock1.2, SW_V1.2
Col6: SW_5.2, SW_B1.2, SW_Delete1.2, SW_F5.2, SW_G1.2, SW_Insert1.2, SW_PrintScreen1.2, SW_T1.2
Col7: SW_6.2, SW_BackSpace1.2, SW_F6.2, SW_F12.2, SW_H1.2, SW_N1.2, SW_Y1.2, SW_|1.2
Col8: SW_7.2, SW_+1.2, SW_?1.2, SW_F7.2, SW_J1.2, SW_M1.2, SW_U1.2, SW_}1.2
Col9: SW_8.2, SW_<1.2, SW_F8.2, SW_F10.2, SW_I1.2, SW_K1.2, SW_RAlt1.2
Col10: SW_0.2, SW_9.2, SW_:1.2, SW_>1.2, SW_F9.2, SW_L1.2, SW_O1.2, SW_P1.2, SW_RMeta1.2
unnamed: A1.3 (GND), A1.8 (GND), A1.13 (GND), A1.18 (GND), A1.23 (GND), A1.28 (GND), A1.38 (GND)
unnamed: D1.2 (A), SW_Esc1.1
unnamed: D2.2 (A), SW_F1.1
unnamed: D3.2 (A), SW_F2.1
unnamed: D4.2 (A), SW_F3.1
unnamed: D5.2 (A), SW_F4.1
unnamed: D6.2 (A), SW_F5.1
unnamed: D7.2 (A), SW_F6.1
unnamed: D8.2 (A), SW_F7.1
unnamed: D9.2 (A), SW_F8.1
unnamed: D10.2 (A), SW_F9.1
unnamed: D11.2 (A), SW_F10.1
unnamed: D12.2 (A_2), SW_F11.1 (1_1)
unnamed: D13.2 (A), SW_F12.1
unnamed: D14.2 (A), SW_PrintScreen1.1
unnamed: D15.2 (A), SW_ScrollLock1.1
unnamed: D16.2 (A), SW_PauseBreak1.1
unnamed: D17.2 (A), SW_~1.1
unnamed: D18.2 (A), SW_1.1
unnamed: D19.2 (A), SW_2.1
unnamed: D20.2 (A), SW_3.1
unnamed: D21.2 (A), SW_4.1
unnamed: D22.2 (A), SW_5.1
unnamed: D23.2 (A), SW_6.1
unnamed: D24.2 (A), SW_7.1
unnamed: D25.2 (A), SW_8.1
unnamed: D26.2 (A), SW_9.1
unnamed: D27.2 (A), SW_0.1
unnamed: D28.2 (A_2), SW_-1.1 (1_1)
unnamed: D29.2 (A), SW_+1.1
unnamed: D30.2 (A), SW_BackSpace1.1
unnamed: D31.2 (A), SW_Insert1.1
unnamed: D32.2 (A), SW_Home1.1
unnamed: D33.2 (A), SW_PageUp1.1
unnamed: D34.2 (A), SW_Tab1.1
unnamed: D35.2 (A), SW_Q1.1
unnamed: D36.2 (A), SW_W1.1
unnamed: D37.2 (A), SW_E1.1
unnamed: D38.2 (A), SW_R1.1
unnamed: D39.2 (A), SW_T1.1
unnamed: D40.2 (A), SW_Y1.1
unnamed: D41.2 (A), SW_U1.1
unnamed: D42.2 (A), SW_I1.1
unnamed: D43.2 (A), SW_O1.1
unnamed: D44.2 (A), SW_P1.1
unnamed: D45.2 (A_2), SW_{1.1 (1_1)
unnamed: D46.2 (A), SW_}1.1
unnamed: D47.2 (A), SW_|1.1
unnamed: D48.2 (A), SW_Delete1.1
unnamed: D49.2 (A), SW_End1.1
unnamed: D50.2 (A), SW_PageDown1.1
unnamed: D51.2 (A), SW_CapsLock1.1
unnamed: D52.2 (A), SW_A1.1
unnamed: D53.2 (A), SW_S1.1
unnamed: D54.2 (A), SW_D1.1
unnamed: D55.2 (A), SW_FF1.1
unnamed: D56.2 (A), SW_G1.1
unnamed: D57.2 (A), SW_H1.1
unnamed: D58.2 (A), SW_J1.1
unnamed: D59.2 (A), SW_K1.1
unnamed: D60.2 (A), SW_L1.1
unnamed: D61.2 (A), SW_:1.1
unnamed: D62.2 (A), SW_"1.1
unnamed: D63.2 (A), SW_Enter1.1
unnamed: D64.2 (A), SW_LShift1.1
unnamed: D65.2 (A), SW_Z1.1
unnamed: D66.2 (A), SW_X1.1
unnamed: D67.2 (A), SW_C1.1
unnamed: D68.2 (A), SW_V1.1
unnamed: D69.2 (A), SW_B1.1
unnamed: D70.2 (A), SW_N1.1
unnamed: D71.2 (A), SW_M1.1
unnamed: D72.2 (A), SW_<1.1
unnamed: D73.2 (A), SW_>1.1
unnamed: D74.2 (A), SW_?1.1
unnamed: D75.2 (A), SW_RShift1.1
unnamed: D76.2 (A), SW_Up1.1
unnamed: D77.2 (A), SW_LCtrl1.1
unnamed: D78.2 (A), SW_LMeta1.1
unnamed: D79.2 (A), SW_LAlt1.1
unnamed: D80.2 (A), SW_Space1.1
unnamed: D81.2 (A), SW_RAlt1.1
unnamed: D82.2 (A), SW_RMeta1.1
unnamed: D83.2 (A), SW_Menu1.1
unnamed: D84.2 (A), SW_RCtrl1.1
unnamed: D85.2 (A), SW_Left1.1
unnamed: D85.1 (K), D86.1 (K)
unnamed: D86.2 (A), SW_Down1.1
unnamed: D87.2 (A), SW_Right1.1
Row1: D1.1 (K), D2.1 (K), D3.1 (K), D4.1 (K), D5.1 (K), D6.1 (K), D7.1 (K), D8.1 (K), D9.1 (K), D10.1 (K)
Row2: D17.1 (K), D18.1 (K), D19.1 (K), D20.1 (K), D21.1 (K), D22.1 (K), D23.1 (K), D24.1 (K), D25.1 (K), D26.1 (K)
Row3: D34.1 (K), D35.1 (K), D36.1 (K), D37.1 (K), D38.1 (K), D39.1 (K), D40.1 (K), D41.1 (K), D42.1 (K), D43.1 (K)
Row4: D51.1 (K), D52.1 (K), D53.1 (K), D54.1 (K), D55.1 (K), D56.1 (K), D57.1 (K), D58.1 (K), D59.1 (K), D60.1 (K)
Row5: D64.1 (K), D65.1 (K), D66.1 (K), D67.1 (K), D68.1 (K), D69.1 (K), D70.1 (K), D71.1 (K), D72.1 (K), D73.1 (K)
Row6: D74.1 (K), D77.1 (K), D78.1 (K), D79.1 (K), D80.1 (K), D81.1 (K), D82.1 (K)
Row7: D11.1 (K), D13.1 (K), D14.1 (K), D15.1 (K), D16.1 (K), D61.1 (K), D62.1 (K), D63.1 (K), D76.1 (K)
Row8: D27.1 (K), D29.1 (K), D30.1 (K), D31.1 (K), D32.1 (K), D33.1 (K), D83.1 (K)
Row9: D44.1 (K), D46.1 (K), D47.1 (K), D48.1 (K), D49.1 (K), D50.1 (K), D75.1 (K), D84.1 (K), D87.1 (K)
